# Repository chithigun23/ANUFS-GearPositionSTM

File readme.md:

# GearSensor STM32

Gear position sensor board for a MoTeC M150 paddle-shift system: an `STM32F072` reads a linear position sensor and the neutral switch, works out the current gear, and reports it to the ECU as an analog voltage, with a CAN transceiver on the ECU bus and status LEDs on the board. Powered from the M150 sensor 5 V or USB-C, and replaces the Arduino UNO R4 WiFi and shield build described on the [GearSensor project page](https://chithigunatilake.com/GearSensor/).

## Architecture

- **Power** - 5 V in from the M150 sensor supply (`SEN_5V`, J3) or from USB-C VBUS (`J1`). A `TPS2116` power mux (`U2`) gives the car priority and falls back to USB when the car rail drops below about 4 V (set by `R3`/`R4`, 300 k / 100 k). It blocks reverse current, so the ECU supply is never back-fed from a laptop and the laptop is never back-fed from the car. The mux status pin goes to `PA2` (`MUX_STAT`: high = car, low = USB). 1 uF on each mux input, a 300 mA polyfuse (`F1`) on the mux output and an `AP2112K-3.3` LDO (`U1`) after it. There is no reverse-polarity stage because a sensor supply cannot be reversed by the battery.
- **Compute** - `STM32F072CB` (`U6`, LQFP-48) with a 24 MHz `ABM8AIG` crystal on HSE, which CAN needs for accurate bit timing. Ferrite-filtered VDDA, NRST and BOOT0 buttons.
- **Position and neutral sensing** - linear position sensor on J3 pin 7, scaled by `R5`/`R6` (10 k / 15 k) so a 5 V sensor swing lands inside the 3.3 V ADC range on `PA0`. Neutral switch on J3 pin 6 into `PB2` through `R28` (1 k). An `AQ1005-01ETG` TVS (`D1`, `D2`) on each harness input.
- **Gear output** - the STM32's own 12-bit DAC on `PA4` (output buffer off, so it can reach 0 V) drives a `TLV9062` op-amp (`U4`) at a gain of 1.5 (`R11` 4.99 k / `R12` 10 k) from the 5 V rail, giving the gear-position voltage on J3 pin 3 up to about 4.1 V through two 390 ohm series resistors (`R29`/`R30`) and a TVS (`D3`). `R10` (1 M) holds the output at 0 V until the firmware enables the DAC. A 10 k / 15 k divider (`R14`/`R15`) reads the output back on `PA1` for closed-loop trim. The unused op-amp channel is tied off as a follower.
- **Status LEDs** - six `XL-2012SURUGC` red/green LEDs: `LED1` to `LED4` show the gear (or a fault) in combination, `LED5` shows MCU status and `LED6` shows the neutral switch. Their anodes share an `LED_5V` rail behind the slide switch `SW3`, which turns every LED off. Each die has its own series resistor (390 ohm red, 680 ohm green) and is sunk by a 5 V-tolerant MCU pin, so no driver is needed.
- **CAN** - `TCAN337` 3.3 V transceiver (`U5`) on `PB9` / `PB8`, with fault on `PB0` and silent mode on `PB1`. CAN+ / CAN- on J3 pins 5 and 4.
- **Debug and USB** - `J1` USB-C with 5.1 k CC pull-downs and a `USBLC6-2SC6` ESD array (`U3`) on D+ / D- into the MCU's native USB (`PA11` / `PA12`). 4-pin SWD header `J2` and a Tag-Connect TC2030 footprint `J4` (pads only, nothing to buy) on the same SWD, reset and 3.3 V nets. Test pads on the rails and every external signal.

The diagram is animated: dashes show the direction of flow, amber for power, teal for signals, blue for buses. If your viewer does not animate SVGs, the arrows still show the same paths.

## Car connector (J3)

| Pin | Net | Function |
|---|---|---|
| 1 | `SEN_5V` | M150 sensor 5 V in |
| 2 | `GND` | Ground |
| 3 | `GEAR_OUT` | Gear voltage out to the ECU |
| 4 | `CAN-` | CAN low |
| 5 | `CAN+` | CAN high |
| 6 | `NEUT_SW` | Neutral switch |
| 7 | `SPS` | Linear position sensor signal |
| 8 | - | Not connected |

## From the Arduino version

- Same job, same sensors, same ECU interface. The shift logic, trust model and FMEA are documented on the [project page](https://chithigunatilake.com/GearSensor/).
- One board replaces the Arduino UNO R4 WiFi and shield.
- The gear-voltage output is read back through an ADC pin again, which version 2 of the Arduino build dropped.
- Status LEDs replace the LED matrix. This board has no WiFi or Bluetooth, so the phone display does not carry over. USB-C and the SWD header are the way in for programming and debug.
- This repo is hardware only. There is no firmware in it yet; the firmware is planned in Rust (see the plan below).

## Status

Work in progress. The schematic is being finished and the PCB is not yet routed. Not run on a car.

## Repo contents

- [KiCad project](gearPosSens.kicad_pro)
- [Schematic](gearPosSens.kicad_sch)
- [PCB layout](gearPosSens.kicad_pcb)
- [Power and gear-output design notes](power-mux-notes.md)
- [Firmware plan](docs/firmware-plan.md) and its [architecture diagram](docs/firmware-architecture.svg)
- [Symbols, footprints and 3D models](library)

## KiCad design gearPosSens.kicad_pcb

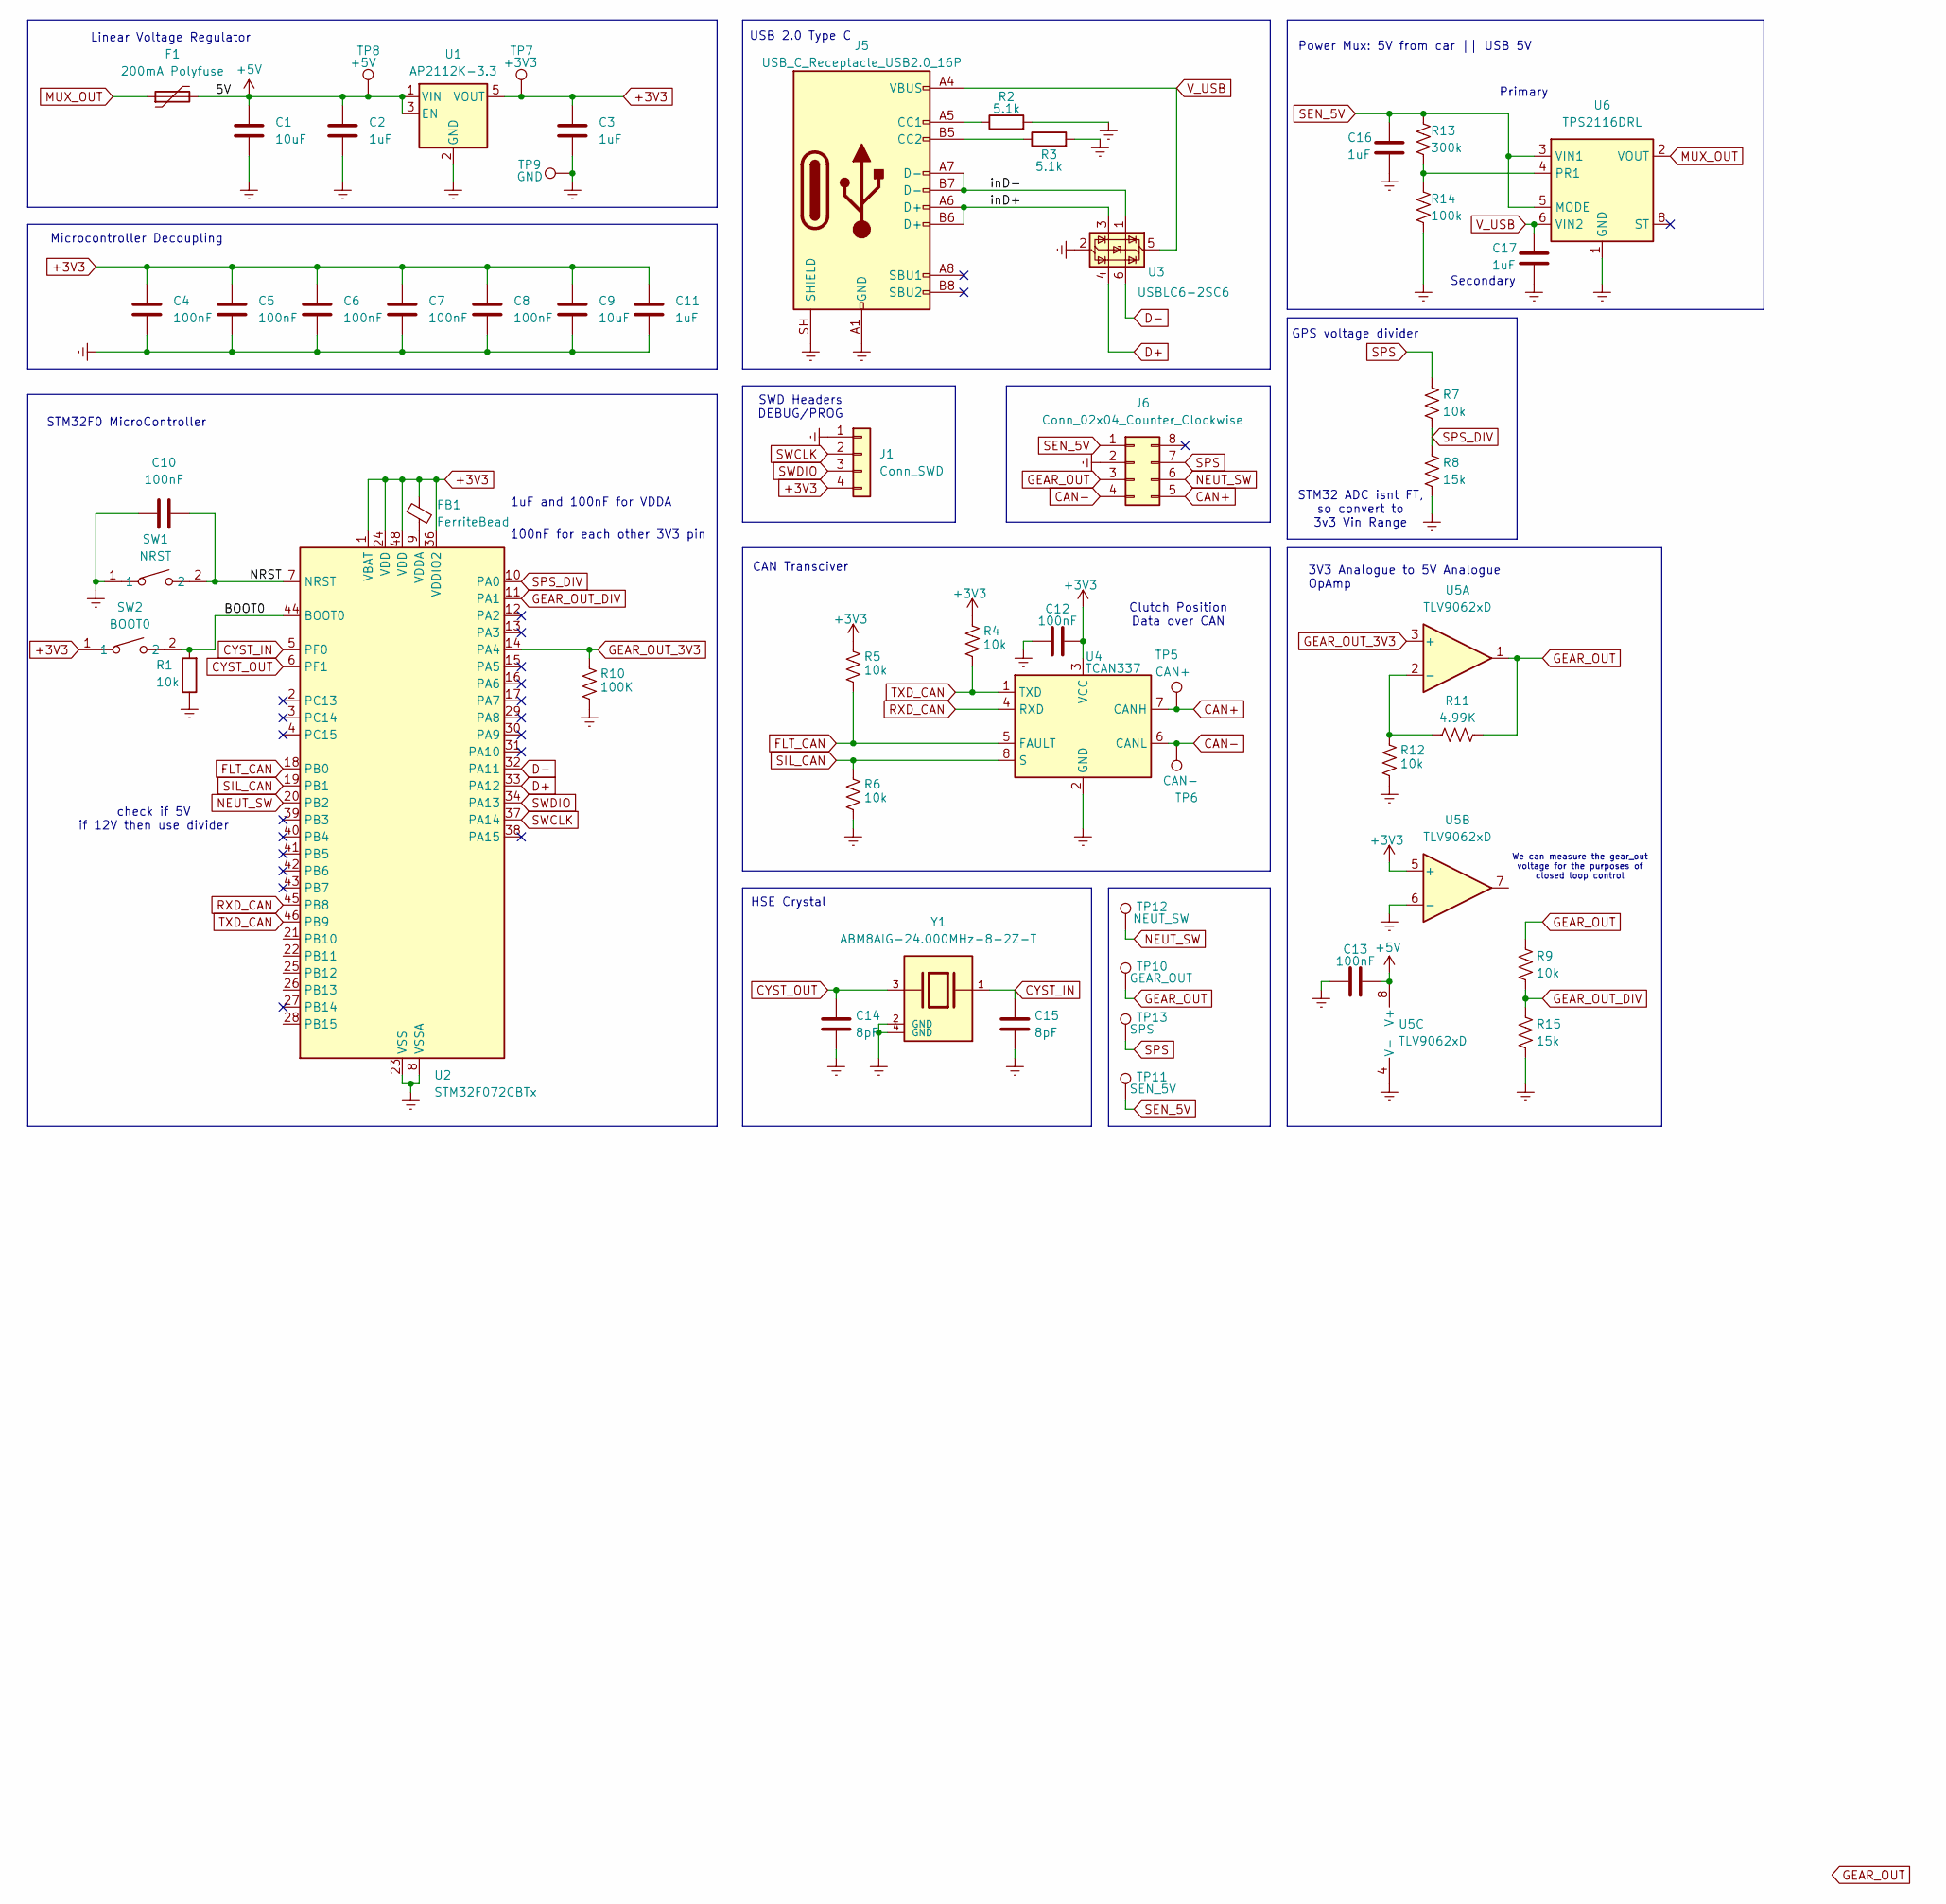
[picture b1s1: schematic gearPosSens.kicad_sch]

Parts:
C1, C9: 10uF; R_0805_2012Metric_Pad1.20x1.40mm_HandSolder
C2, C3, C11, C16, C17: 1uF; R_0805_2012Metric_Pad1.20x1.40mm_HandSolder
C4, C5, C6, C7, C8, C10, C12, C13: 100nF; R_0805_2012Metric_Pad1.20x1.40mm_HandSolder
C14, C15: 8pF; C_0402_1005Metric_Pad0.74x0.62mm_HandSolder
F1: 200mA Polyfuse; C_0603_1608Metric_Pad1.08x0.95mm_HandSolder
FB1: FerriteBead; C_0603_1608Metric_Pad1.08x0.95mm_HandSolder
J1: Conn_SWD; PinHeader_1x04_P2.54mm_Vertical
J5: USB_C_Receptacle_USB2.0_16P; USB-C-SMD_TYPE-C-16PIN-2MD-073
J6: Conn_02x04_Counter_Clockwise
R1, R4, R5, R6, R7, R9, R12: 10k; R_0805_2012Metric_Pad1.20x1.40mm_HandSolder
R2, R3: 5.1k; R_0805_2012Metric_Pad1.20x1.40mm_HandSolder
R8, R15: 15k; R_0805_2012Metric_Pad1.20x1.40mm_HandSolder
R10: 100K; R_0805_2012Metric_Pad1.20x1.40mm_HandSolder
R11: 4.99K
R13: 300k; R_0805_2012Metric_Pad1.20x1.40mm_HandSolder
R14: 100k; R_0805_2012Metric_Pad1.20x1.40mm_HandSolder
SW1: NRST; SW-SMD_L3.9-W3.0-P4.45; MPN TS-1088-AR02016; LCSC Part C720477
SW2: BOOT0; SW-SMD_L3.9-W3.0-P4.45; MPN TS-1088-AR02016; LCSC Part C720477
TP5: CAN+; TestPoint_THTPad_D2.0mm_Drill1.0mm
TP6: CAN-; TestPoint_THTPad_D2.0mm_Drill1.0mm
TP7: +3V3; TestPoint_THTPad_D2.0mm_Drill1.0mm
TP8: +5V; TestPoint_THTPad_D2.0mm_Drill1.0mm
TP9: GND; TestPoint_THTPad_D2.0mm_Drill1.0mm
TP10: GEAR_OUT; TestPoint_THTPad_D2.0mm_Drill1.0mm
TP11: SEN_5V; TestPoint_THTPad_D2.0mm_Drill1.0mm
TP12: NEUT_SW; TestPoint_THTPad_D2.0mm_Drill1.0mm
TP13: SPS; TestPoint_THTPad_D2.0mm_Drill1.0mm
U1: AP2112K-3.3; SOT-23-5_HandSoldering
U2: STM32F072CBTx; LQFP-48_7x7mm_P0.5mm
U3: USBLC6-2SC6; SOT-23-6
U4: TCAN337; SOIC-8_3.9x4.9mm_P1.27mm
U5: TLV9062xD; SOIC-8_3.9x4.9mm_P1.27mm
U6: TPS2116DRL; SOT-583-8
Y1: ABM8AIG-24.000MHz-8-2Z-T; ABM8AIG-24.000MHZ-8-2Z-T; PARTREV 43629

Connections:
+3V3: C3.1, C4.2, C5.2, C6.2, C7.2, C8.2, C9.2, C11.1, C12.2, FB1.1, J1.4, R4.1, R5.1, SW2.1, TP7.1 (1_1), U1.5 (VOUT), U2.1 (VBAT), U2.24 (VDD), U2.36 (VDDIO2), U2.48 (VDD), U4.3 (VCC), U5.5 (+); also elsewhere on the board
/BOOT0: R1.2, SW2.2, U2.44 (BOOT0)
/NRST: C10.2, SW1.2, U2.7 (NRST)
/inD+: J5.A6 (D+), J5.B6 (D+), U3.3 (I/O2)
/inD-: J5.A7 (D-), J5.B7 (D-), U3.1 (I/O1)
CAN+: J6.5, TP5.1 (1_1), U4.7 (CANH); also elsewhere on the board
CAN-: J6.4, TP6.1 (1_1), U4.6 (CANL); also elsewhere on the board
CYST_IN: C15.1, U2.5 (PF0), Y1.1
CYST_OUT: C14.1, U2.6 (PF1), Y1.3
D+: U2.33 (PA12), U3.4 (I/O2)
D-: U2.32 (PA11), U3.6 (I/O1)
FLT_CAN: R5.2, U2.18 (PB0), U4.5 (FAULT)
GEAR_OUT: J6.3, R9.1, R11.2, TP10.1 (1_1), U5.1
GEAR_OUT_3V3: R10.1, U2.14 (PA4), U5.3 (+)
GEAR_OUT_DIV: R9.2, R15.1, U2.11 (PA1)
GND: C1.1, C2.2, C3.2, C4.1, C5.1, C6.1, C7.1, C8.1, C9.1, C10.1, C11.2, C12.1, C13.1, C14.2, C15.2, C16.1, C17.1, J1.1, J5.A1 (GND), J5.A12 (GND), J5.B1 (GND), J5.B12 (GND), J5.SH (SHIELD), J6.2, R1.1, R2.2, R3.2, R6.2, R8.2, R10.2, R12.2, R14.2, R15.2, SW1.1, TP9.1 (1_1), U1.2 (GND), U2.8 (VSSA), U2.23 (VSS), U2.35 (VSS), U2.47 (VSS), U3.2 (GND), U4.2 (GND), U5.4 (V-), U5.6 (-), U6.1 (GND), Y1.2 (GND), Y1.4 (GND)
NEUT_SW: J6.6, TP12.1 (1_1), U2.20 (PB2)
unnamed: J5.A5 (CC1), R2.1
unnamed: J5.B5 (CC2), R3.1
unnamed: FB1.2, U2.9 (VDDA)
unnamed: R11.1, R12.1, U5.2 (-)
unnamed: R13.2, R14.1, U6.4 (PR1)
RXD_CAN: U2.45 (PB8), U4.4 (RXD)
SEN_5V: C16.2, J6.1, R13.1, TP11.1 (1_1), U6.3 (VIN1), U6.5 (MODE)
SIL_CAN: R6.1, U2.19 (PB1), U4.8 (S)
SPS: J6.7, R7.1, TP13.1 (1_1)
SPS_DIV: R7.2, R8.1, U2.10 (PA0)
SWCLK: J1.2, U2.37 (PA14)
SWDIO: J1.3, U2.34 (PA13)
TXD_CAN: R4.2, U2.46 (PB9), U4.1 (TXD)
V_USB: C17.2, J5.A4 (VBUS), J5.A9 (VBUS), J5.B4 (VBUS), J5.B9 (VBUS), U3.5 (VBUS), U6.6 (VIN2)

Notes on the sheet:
We can measure the gear_out voltage for the purposes of closed loop control
GPS voltage divider
100nF for each other 3V3 pin
Microcontroller Decoupling
3V3 Analogue to 5V Analogue OpAmp
CAN Transciver
Secondary
SWD Headers DEBUG/PROG
Power Mux: 5V from car || USB 5V
HSE Crystal
1uF and 100nF for VDDA
Clutch Position Data over CAN
USB 2.0 Type C
Linear Voltage Regulator
check if 5V if 12V then use divider
Primary
STM32F0 MicroController
STM32 ADC isnt FT, so convert to 3v3 Vin Range

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
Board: 4 copper layers, 56 parts (0 on the bottom side), 33 nets, no tracks yet.

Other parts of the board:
TP14: +3V3; TestPoint_THTPad_D2.0mm_Drill1.0mm
TP15: CAN+; TestPoint_THTPad_D2.0mm_Drill1.0mm
TP16: CAN-; TestPoint_THTPad_D2.0mm_Drill1.0mm

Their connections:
+3V3: TP14.1 (1_1); also elsewhere on the board
CAN+: TP15.1 (1_1); also elsewhere on the board
CAN-: TP16.1 (1_1); also elsewhere on the board
